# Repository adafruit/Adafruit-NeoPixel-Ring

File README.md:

# Adafruit NeoPixel Rings

&nbsp; 
&nbsp; 
<br />

Buy these products in the Adafruit Shop:

- [16 NeoPixel Ring](http://www.adafruit.com/products/1463)
- [24 NeoPixel Ring](http://www.adafruit.com/products/1586)
- [12 NeoPixel Ring](http://www.adafruit.com/products/1643)

These ultra bright smart LED NeoPixels are arranged in a circle. The rings are 'chainable' - connect the output pin of one to the input pin of another. Use only one microcontroller pin to control as many as you can chain together! Each LED is addressable as the driver chip is inside the LED. Each one has ~18mA constant current drive so the color will be very consistent even if the voltage varies, and no external choke resistors are required making the design slim. Power the whole thing with 5VDC (4-7V works) and you're ready to rock.

There is a single data line with a very timing-specific protocol. Since the protocol is very sensitive to timing, it requires a real-time microconroller such as an AVR, Adafruit Metro/Trinket/Gemma, Arduino, etc. It cannot be used with a Linux-based microcomputer or interpreted microcontroller such as the Raspberry Pi, netduino or Basic Stamp. Our wonderfully-written NeoPixel libraries in Arduino and CircuitPython supports these pixels! 

PCB files for Adafruit NeoPixel Rings in 12, 16 and 24 pixels!

### License

Adafruit invests time and resources providing this open source design, please support Adafruit and open-source hardware by purchasing products from [Adafruit](https://www.adafruit.com)!

All text above must be included in any redistribution

Designed by Limor Fried/Ladyada for Adafruit Industries.
Creative Commons Attribution/Share-Alike, all text above must be included in any redistribution. 
See license.txt for additional information.

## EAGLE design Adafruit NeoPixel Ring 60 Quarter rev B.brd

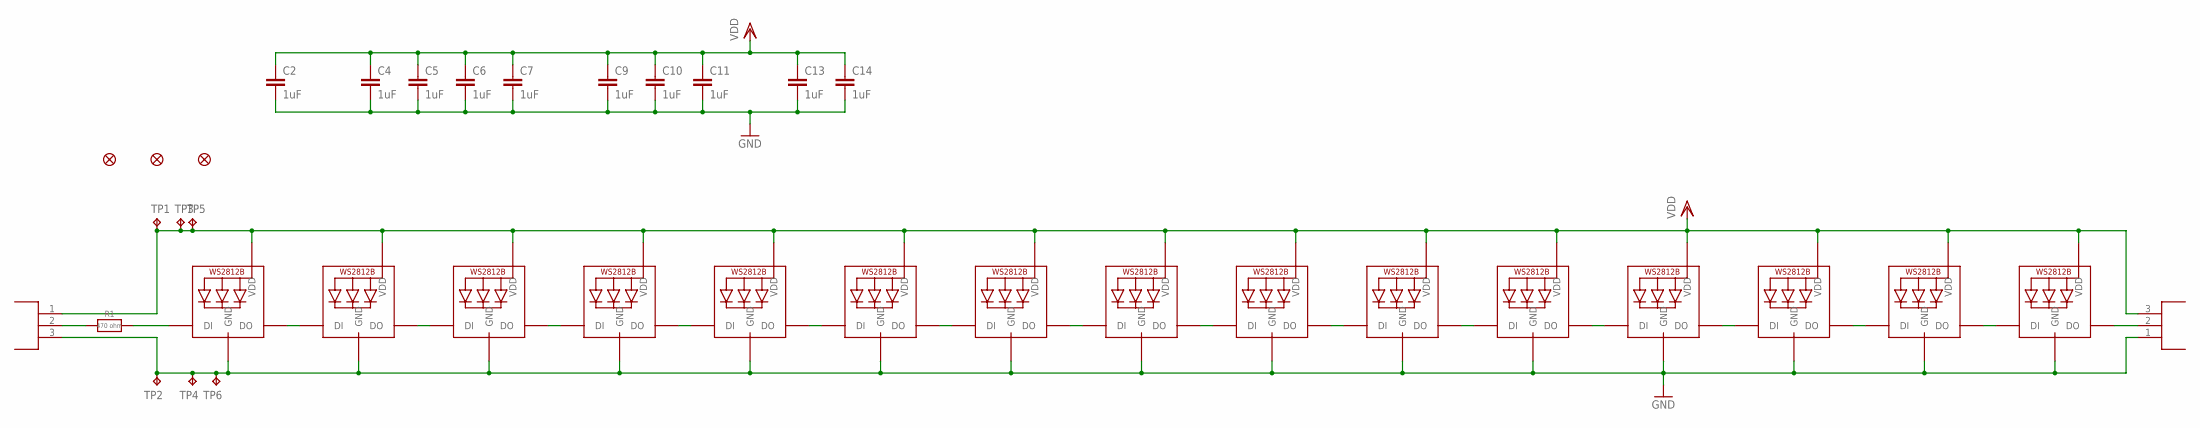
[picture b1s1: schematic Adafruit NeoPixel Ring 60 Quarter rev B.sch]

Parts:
C2, C4, C5, C6, C7, C9, C10, C11, C13, C14: 1uF; C0603
FID1, FID2, FID3: FIDUCIAL_1MM
LED1, LED2, LED3, LED4, LED5, LED6, LED7, LED8, LED9, LED10, LED11, LED12, LED13, LED14, LED15: WS2812B_5050N; WS2812B-NARROW
R1: 470 ohm; 0603-NO
TP1, TP2, TP3, TP4, TP5, TP6: TPTP20R; TP20R
U$1, U$2: DNP; RING_END_CONN_X3

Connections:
GND: C2.2, C4.2, C5.2, C6.2, C7.2, C9.2, C10.2, C11.2, C13.2, C14.2, LED1.3-GND (GND), LED2.3-GND (GND), LED3.3-GND (GND), LED4.3-GND (GND), LED5.3-GND (GND), LED6.3-GND (GND), LED7.3-GND (GND), LED8.3-GND (GND), LED9.3-GND (GND), LED10.3-GND (GND), LED11.3-GND (GND), LED12.3-GND (GND), LED13.3-GND (GND), LED14.3-GND (GND), LED15.3-GND (GND), TP2.TP, TP4.TP, TP6.TP, U$1.3, U$2.1
unnamed: LED1.2-DOUT (DO), LED2.4-DIN (DI)
unnamed: LED2.2-DOUT (DO), LED3.4-DIN (DI)
unnamed: LED3.2-DOUT (DO), LED4.4-DIN (DI)
unnamed: LED4.2-DOUT (DO), LED5.4-DIN (DI)
unnamed: LED5.2-DOUT (DO), LED6.4-DIN (DI)
unnamed: LED6.2-DOUT (DO), LED7.4-DIN (DI)
unnamed: LED7.2-DOUT (DO), LED8.4-DIN (DI)
unnamed: LED8.2-DOUT (DO), LED9.4-DIN (DI)
unnamed: LED9.2-DOUT (DO), LED10.4-DIN (DI)
unnamed: LED10.2-DOUT (DO), LED11.4-DIN (DI)
unnamed: LED11.2-DOUT (DO), LED12.4-DIN (DI)
unnamed: LED12.2-DOUT (DO), LED13.4-DIN (DI)
unnamed: LED13.2-DOUT (DO), LED14.4-DIN (DI)
unnamed: LED14.2-DOUT (DO), LED15.4-DIN (DI)
unnamed: LED1.4-DIN (DI), R1.2
unnamed: LED15.2-DOUT (DO), U$2.2
unnamed: R1.1, U$1.2
VDD: C2.1, C4.1, C5.1, C6.1, C7.1, C9.1, C10.1, C11.1, C13.1, C14.1, LED1.1-VDD (VDD), LED2.1-VDD (VDD), LED3.1-VDD (VDD), LED4.1-VDD (VDD), LED5.1-VDD (VDD), LED6.1-VDD (VDD), LED7.1-VDD (VDD), LED8.1-VDD (VDD), LED9.1-VDD (VDD), LED10.1-VDD (VDD), LED11.1-VDD (VDD), LED12.1-VDD (VDD), LED13.1-VDD (VDD), LED14.1-VDD (VDD), LED15.1-VDD (VDD), TP1.TP, TP3.TP, TP5.TP, U$1.1, U$2.3

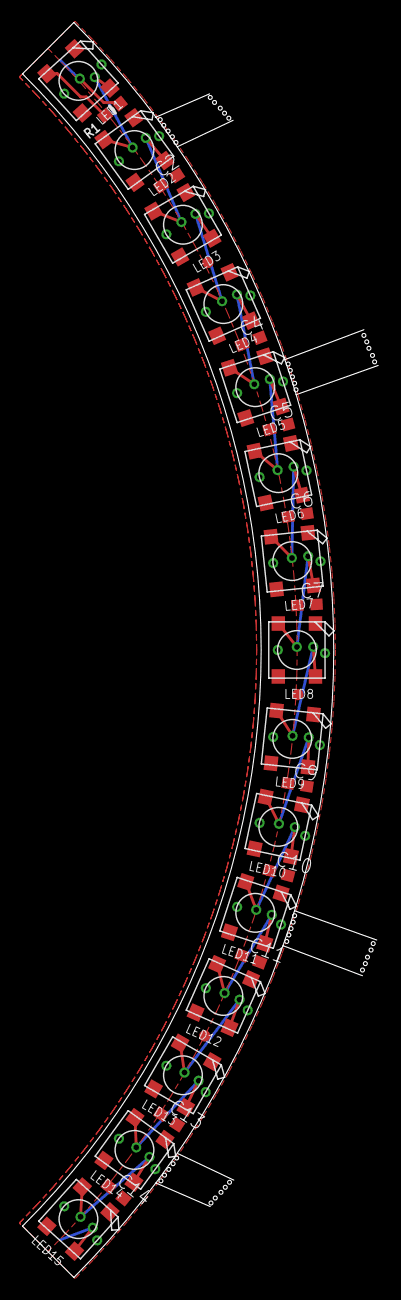
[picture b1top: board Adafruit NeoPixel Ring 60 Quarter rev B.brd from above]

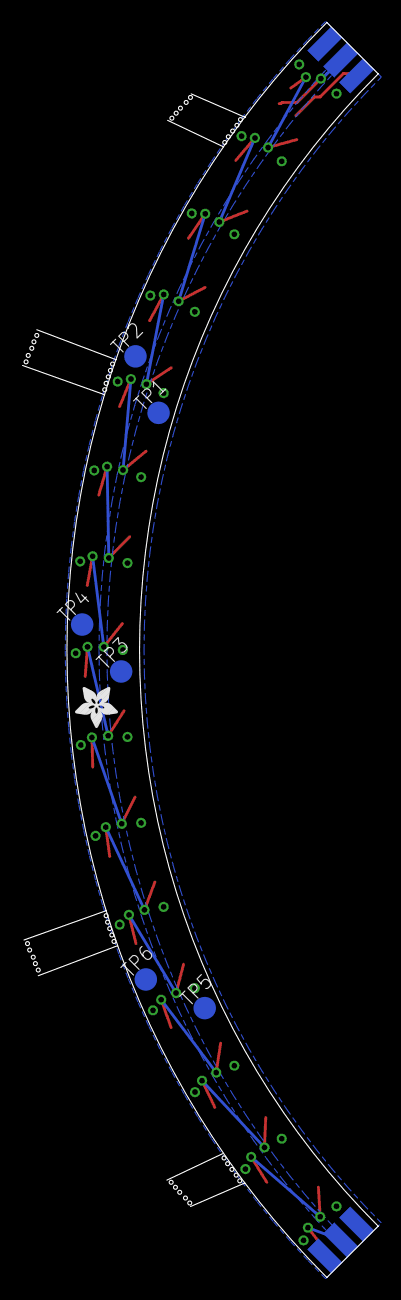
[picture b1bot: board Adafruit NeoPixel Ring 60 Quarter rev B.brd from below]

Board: 2 copper layers, 31.6 x 111.5 mm, 52 parts (23 on the bottom side), 19 nets.

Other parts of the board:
PLABEL0: PLABEL0
PLABEL1: PLABEL1
PLABEL2: PLABEL2
PLABEL3: PLABEL3
PLABEL4: PLABEL4
PLABEL5: PLABEL5
PLABEL6: PLABEL6
PLABEL7: PLABEL7
PLABEL8: PLABEL8
PLABEL9: PLABEL9
PLABEL10: PLABEL10
PLABEL11: PLABEL11
PLABEL12: PLABEL12
PLABEL13: PLABEL13
U$3: ADAFRUIT_3.5MM

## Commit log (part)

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2014-01-13 12 16 & 24!
2014-01-13 readdd
2014-04-17 B revision for 24 ring
2014-11-11 added v2 of the 16 ring!
2015-01-14 60 quarter!

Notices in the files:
parts and their libraries:
microbuilder: This work is placed in the public domain, and may be freely used for commercial and non-commercial work with the following conditions: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
